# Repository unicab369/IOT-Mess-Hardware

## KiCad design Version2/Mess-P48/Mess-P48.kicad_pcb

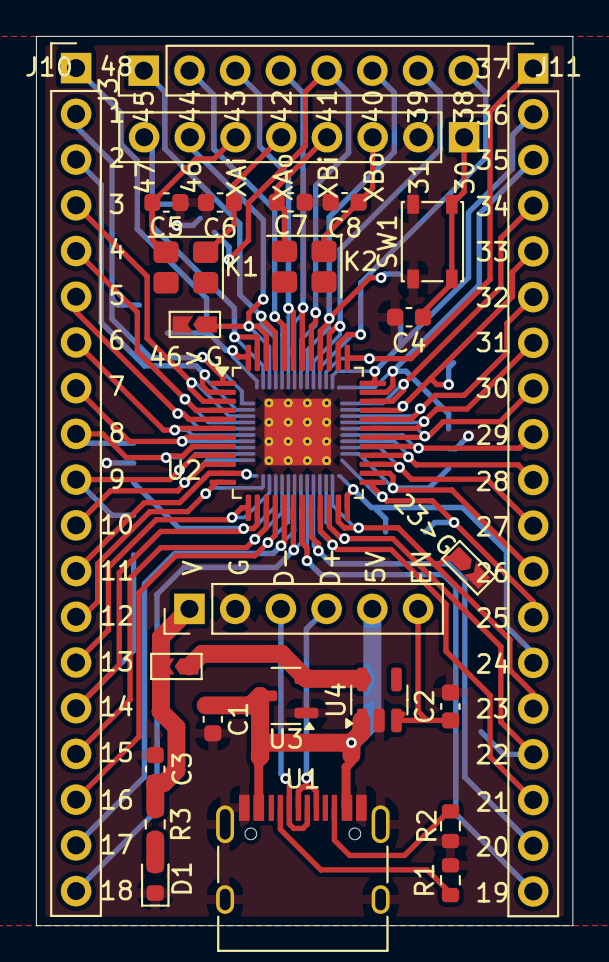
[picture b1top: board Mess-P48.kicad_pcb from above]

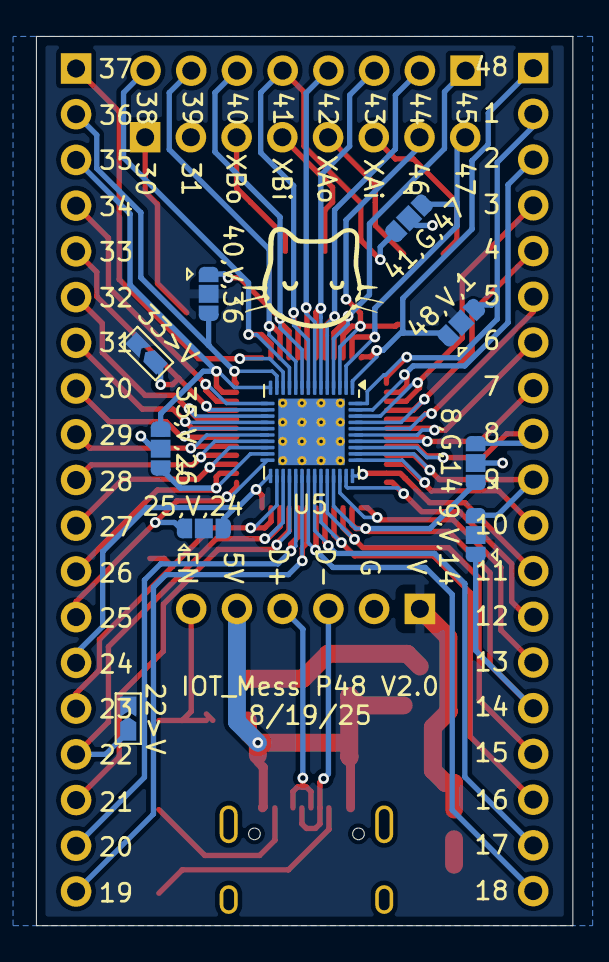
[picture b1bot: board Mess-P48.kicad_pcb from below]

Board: 2 copper layers, 29.8 x 49.4 mm, 37 parts (10 on the bottom side), 63 nets.

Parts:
8,G,14, 9,V,14, 25,V,24, 35,V,26, 40,V,36, 41,G,47, 48,V,1: Jumper; Jumper-3_P1.3mm_Open_RoundedPad1.0x1.5mm
22>V, 23>G, 33>V, 46>G: Jumper_2; Jumpper-triangle
C1: 10u; C_0603_1608Metric
C2, C3: 1u; C_0603_1608Metric
C4: .1u; C_0603_1608Metric
C5, C6: 15-30pF; C_0603_1608Metric
C7, C8: 12-25pF; C_0603_1608Metric
D1: LED; LED_0603_1608Metric
J1: Jumper_2; Jumpper-triangle
J2: Conn_01x06_Pin; PinHeader_1x06_P2.54mm_Vertical
J3, J4: Conn_01x08_Pin; PinHeader_1x08_P2.54mm_Vertical
J10, J11: Conn_01x19_Pin; PinHeader_1x19_P2.54mm_Vertical
K1, K2: Crystal; Crystal_SMD_3225-4Pin_3.2x2.5mm
R1, R2: 5.1K; R_0603_1608Metric
R3: R; R_0603_1608Metric
SW1: SW_Push; SW_SPST_PTS810
U1: USB_C_Receptacle_USB2.0_16P; USB_C_Receptacle_HRO_TYPE-C-31-M-12
U2: LQFP-48-1EP_7x7mm_P0.5mm_EP3.6x3.6mm
U3: XC6206PxxxMR; SOT-23-3
U4: ME6211C33M5; SOT-23-5
U5: CH32L103C8T6; QFN-48-1EP_5x5mm_P0.35mm_EP3.7x3.7mm_ThermalVias

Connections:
5V: C1.1, J2.5, U1.A4 (VBUS), U1.A9 (VBUS), U1.B4 (VBUS), U1.B9 (VBUS), U3.3 (VI), U4.1 (V_{IN})
D+: J2.4, U1.A6 (D+), U1.B6 (D+)
D-: J2.3, U1.A7 (D-), U1.B7 (D-)
EN: C2.1, J2.6, U4.3 (CE)
GND: 8,G,14.2 (C), 23>G.2 (B), 35,V,26.2 (C), 41,G,47.2 (C), 46>G.2 (B), C1.2, C2.2, C3.2, C4.2, C5.2, C6.2, C7.2, C8.2, D1.1 (K), J2.2, J4.2, R1.2, R2.2, SW1.2, U1.A1 (GND), U1.A12 (GND), U1.B1 (GND), U1.B12 (GND), U1.S1 (SHIELD), U2.49 (VSS), U3.1 (GND), U4.2 (V_{SS}), U5.49 (VSS)
unnamed: D1.2 (A), R3.2
unnamed: J1.1 (A), U3.2 (VO), U4.5 (V_{OUT})
unnamed: C4.1, J4.1, SW1.1
unnamed: C8.1, J4.3, K2.1
unnamed: C7.1, J4.4, K2.2
unnamed: C6.1, J4.5, K1.1
unnamed: C5.1, J4.6, K1.2
unnamed: R1.1, U1.A5 (CC1)
unnamed: R2.1, U1.B5 (CC2)
P_1: 48,V,1.3 (B), J10.2, U2.1 (VBAT), U5.48 (VDD_3)
P_2: J10.3, U2.2 (PC13), U5.47 (VSS_3)
P_3: J10.4, U2.3 (PC14/OSC32_IN), U5.46 (PB9)
P_4: J10.5, U2.4 (PC15/OSC32_OUT), U5.45 (PB8)
P_5: J10.6, U2.5 (PD0/OSC_IN), U5.44 (BOOT0)
P_6: J10.7, U2.6 (PD1/OSC_OUT), U5.43 (PB7/USB2_DP/SDA*)
P_7: J10.8, U2.7 (NRST), U5.42 (PB6/USB2_DM/SCL*)
P_8: 8,G,14.3 (B), J10.9, U2.8 (VSSA), U5.41 (PB5)
P_9: 9,V,14.3 (B), J10.10, U2.9 (VDDA), U5.40 (PB4)
P_10: J10.11, U2.10 (PA0/ADC0/WKUP), U5.39 (PB3)
P_11: J10.12, U2.11 (PA1/ADC1), U5.38 (PA15)
P_12: J10.13, U2.12 (PA2/ADC2), U5.37 (PA14/SWCLK)
P_13: J10.14, U2.13 (PA3/ADC3), U5.36 (VDD_2)
P_14: 8,G,14.1 (A), 9,V,14.1 (A), J10.15, U2.14 (PA4/ADC), U5.35 (VSS_2)
P_15: J10.16, U2.15 (PA5/ADC5/SCK*), U5.34 (PA23/SWDIO)
P_16: J10.17, U2.16 (PA6/ADC6/MISO*), U5.33 (PA12/USB_HDP)
P_17: J10.18, U2.17 (PA7/ADC7/MOSI*), U5.32 (PA11/USB_HDM)
P_18: J10.19, U2.18 (PB0/ADC8), U5.31 (PA10)
P_19: J11.19, U2.19 (PB1/ADC9), U5.30 (PA9)
P_20: J11.18, U2.20 (PB2/BOTT), U5.29 (PA8)
P_21: J11.17, U2.21 (PB10/SCL2*), U5.28 (PD15/MOSI_2*)
P_22: 22>V.1 (A), J11.16, U2.22 (PB11/SDA2*), U5.27 (PD14/MISO_2*)
P_23: 23>G.1 (A), J11.15, U2.23 (VSS_1), U5.26 (PD13/SCK_2*)
P_24: 25,V,24.3 (B), J11.14, U2.24 (VDD_VIO_1), U5.25 (PD12)
P_25: 25,V,24.1 (A), J11.13, U2.25 (PB12), U5.24 (VDD_1)
P_26: 35,V,26.1 (A), J11.12, U2.26 (PB13/SCK2*), U5.23 (VSS_1)
P_27: J11.11, U2.27 (PB14/MISO2*), U5.22 (BP11/SDA2*)
P_28: J11.10, U2.28 (PB15/MOSI2*), U5.21 (PB10/SCL2*)
P_29: J11.9, U2.29 (PA8), U5.20 (PB2/BOOT)
P_30: J11.8, U2.30 (PA9), U5.19 (PB1/ADC9)
P_31: J11.7, U2.31 (PA10), U5.18 (PB0/ADC8)
P_32: J11.6, U2.32 (PA11/USB1_DM), U5.17 (PA7/ADC7/MOSI*)
P_33: 33>V.1 (A), J11.5, U2.33 (PA12/USB1_DP), U5.16 (PA6/ADC6/MISO*)
P_34: J11.4, U2.34 (AP13/SWDIO), U5.15 (PA5/ADC5/ADC1/SCK*)
P_35: 35,V,26.3 (B), J11.3, U2.35 (VSS_2), U5.14 (PA4/ADC4/ADC0)
P_36: 40,V,36.3 (B), J11.2, U2.36 (VDD_2), U5.13 (PA3/ADC3)
P_37: J11.1, U2.37 (PA14/SWCLK), U5.12 (PA2/ADC2)
P_38: J3.8, U2.38 (PA15), U5.11 (PA1/ADC1)
P_39: J3.7, U2.39 (PB3), U5.10 (PA0/ADC0/WKUP)
P_40: 40,V,36.1 (A), J3.6, U2.40 (PB4), U5.9 (VDDA)
P_41: 41,G,47.3 (B), J3.5, U2.41 (PB5), U5.8 (VSSA)
P_42: J3.4, U2.42 (PB6/USB2_DM/SCL*), U5.7 (NRST)
P_43: J3.3, U2.43 (PB7/USB2_DP/SDA*), U5.6 (PD1/OSC_OUT)
P_44: J3.2, U2.44 (BOOT0), U5.5 (PD0/OSC_IN)
P_45: J3.1, U2.45 (PB8), U5.4 (PC15/OSC32_OUT)
P_46: 46>G.1 (A), J4.7, U2.46 (PB9), U5.3 (PC14/OSC32_IN)
P_47: 41,G,47.1 (A), J4.8, U2.47 (VSS_3), U5.2 (PC13)
P_48: 48,V,1.1 (A), J10.1, U2.48 (VDD_VIO_3), U5.1 (VBAT)
VCC: 9,V,14.2 (C), 22>V.2 (B), 25,V,24.2 (C), 33>V.2 (B), 40,V,36.2 (C), 48,V,1.2 (C), C3.1, J1.2 (B), J2.1, R3.1

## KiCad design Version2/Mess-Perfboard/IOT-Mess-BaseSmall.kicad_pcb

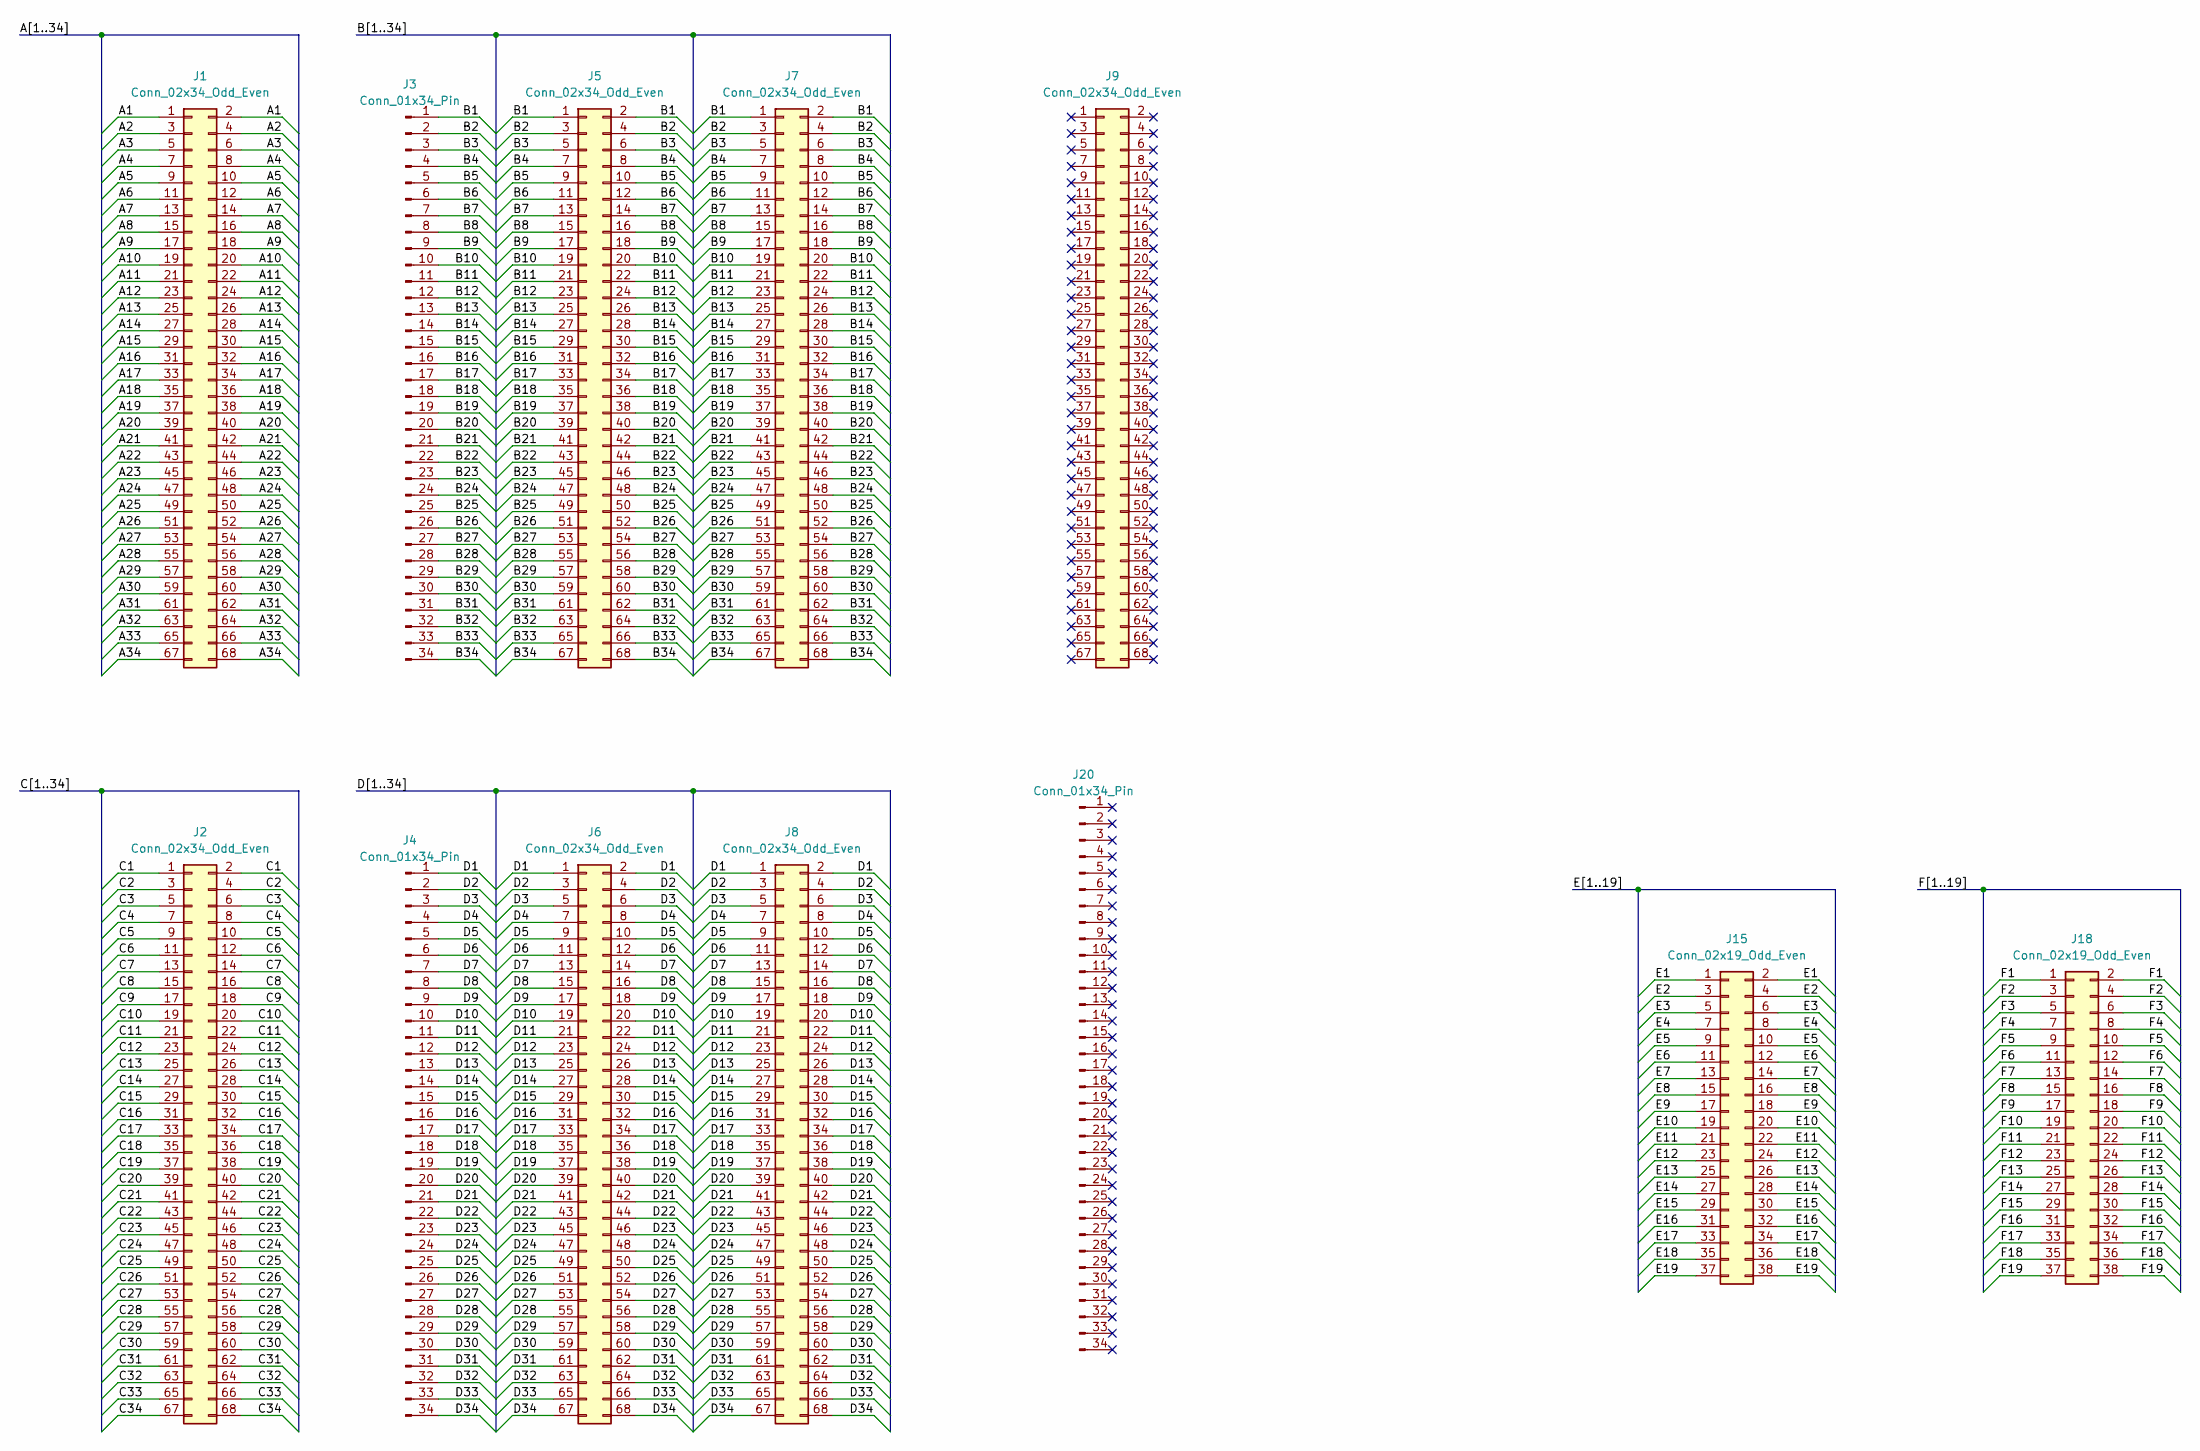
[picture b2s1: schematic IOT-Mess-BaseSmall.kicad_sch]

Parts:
J1, J2, J5, J6, J7, J8, J9: Conn_02x34_Odd_Even; PinSocket_2x34_P2.54mm_Vertical
J3, J4, J20: Conn_01x34_Pin; PinHeader_1x34_P2.54mm_Vertical
J15, J18: Conn_02x19_Odd_Even; PinHeader_2x19_P2.54mm_Vertical

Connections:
/A1: J1.1, J1.2
/A2: J1.3, J1.4
/A3: J1.5, J1.6
/A4: J1.7, J1.8
/A5: J1.9, J1.10
/A6: J1.11, J1.12
/A7: J1.13, J1.14
/A8: J1.15, J1.16
/A9: J1.17, J1.18
/A10: J1.19, J1.20
/A11: J1.21, J1.22
/A12: J1.23, J1.24
/A13: J1.25, J1.26
/A14: J1.27, J1.28
/A15: J1.29, J1.30
/A16: J1.31, J1.32
/A17: J1.33, J1.34
/A18: J1.35, J1.36
/A19: J1.37, J1.38
/A20: J1.39, J1.40
/A21: J1.41, J1.42
/A22: J1.43, J1.44
/A23: J1.45, J1.46
/A24: J1.47, J1.48
/A25: J1.49, J1.50
/A26: J1.51, J1.52
/A27: J1.53, J1.54
/A28: J1.55, J1.56
/A29: J1.57, J1.58
/A30: J1.59, J1.60
/A31: J1.61, J1.62
/A32: J1.63, J1.64
/A33: J1.65, J1.66
/A34: J1.67, J1.68
/B1: J3.1, J5.1, J5.2, J7.1, J7.2
/B2: J3.2, J5.3, J5.4, J7.3, J7.4
/B3: J3.3, J5.5, J5.6, J7.5, J7.6
/B4: J3.4, J5.7, J5.8, J7.7, J7.8
/B5: J3.5, J5.9, J5.10, J7.9, J7.10
/B6: J3.6, J5.11, J5.12, J7.11, J7.12
/B7: J3.7, J5.13, J5.14, J7.13, J7.14
/B8: J3.8, J5.15, J5.16, J7.15, J7.16
/B9: J3.9, J5.17, J5.18, J7.17, J7.18
/B10: J3.10, J5.19, J5.20, J7.19, J7.20
/B11: J3.11, J5.21, J5.22, J7.21, J7.22
/B12: J3.12, J5.23, J5.24, J7.23, J7.24
/B13: J3.13, J5.25, J5.26, J7.25, J7.26
/B14: J3.14, J5.27, J5.28, J7.27, J7.28
/B15: J3.15, J5.29, J5.30, J7.29, J7.30
/B16: J3.16, J5.31, J5.32, J7.31, J7.32
/B17: J3.17, J5.33, J5.34, J7.33, J7.34
/B18: J3.18, J5.35, J5.36, J7.35, J7.36
/B19: J3.19, J5.37, J5.38, J7.37, J7.38
/B20: J3.20, J5.39, J5.40, J7.39, J7.40
/B21: J3.21, J5.41, J5.42, J7.41, J7.42
/B22: J3.22, J5.43, J5.44, J7.43, J7.44
/B23: J3.23, J5.45, J5.46, J7.45, J7.46
/B24: J3.24, J5.47, J5.48, J7.47, J7.48
/B25: J3.25, J5.49, J5.50, J7.49, J7.50
/B26: J3.26, J5.51, J5.52, J7.51, J7.52
/B27: J3.27, J5.53, J5.54, J7.53, J7.54
/B28: J3.28, J5.55, J5.56, J7.55, J7.56
/B29: J3.29, J5.57, J5.58, J7.57, J7.58
/B30: J3.30, J5.59, J5.60, J7.59, J7.60
/B31: J3.31, J5.61, J5.62, J7.61, J7.62
/B32: J3.32, J5.63, J5.64, J7.63, J7.64
/B33: J3.33, J5.65, J5.66, J7.65, J7.66
/B34: J3.34, J5.67, J5.68, J7.67, J7.68
/C1: J2.1, J2.2
/C2: J2.3, J2.4
/C3: J2.5, J2.6
/C4: J2.7, J2.8
/C5: J2.9, J2.10
/C6: J2.11, J2.12
/C7: J2.13, J2.14
/C8: J2.15, J2.16
/C9: J2.17, J2.18
/C10: J2.19, J2.20
/C11: J2.21, J2.22
/C12: J2.23, J2.24
/C13: J2.25, J2.26
/C14: J2.27, J2.28
/C15: J2.29, J2.30
/C16: J2.31, J2.32
/C17: J2.33, J2.34
/C18: J2.35, J2.36
/C19: J2.37, J2.38
/C20: J2.39, J2.40
/C21: J2.41, J2.42
/C22: J2.43, J2.44
/C23: J2.45, J2.46
/C24: J2.47, J2.48
/C25: J2.49, J2.50
/C26: J2.51, J2.52
/C27: J2.53, J2.54
/C28: J2.55, J2.56
/C29: J2.57, J2.58
/C30: J2.59, J2.60
/C31: J2.61, J2.62
/C32: J2.63, J2.64
/C33: J2.65, J2.66
/C34: J2.67, J2.68
/D1: J4.1, J6.1, J6.2, J8.1, J8.2
/D2: J4.2, J6.3, J6.4, J8.3, J8.4
/D3: J4.3, J6.5, J6.6, J8.5, J8.6
/D4: J4.4, J6.7, J6.8, J8.7, J8.8
/D5: J4.5, J6.9, J6.10, J8.9, J8.10
/D6: J4.6, J6.11, J6.12, J8.11, J8.12
/D7: J4.7, J6.13, J6.14, J8.13, J8.14
/D8: J4.8, J6.15, J6.16, J8.15, J8.16
/D9: J4.9, J6.17, J6.18, J8.17, J8.18
/D10: J4.10, J6.19, J6.20, J8.19, J8.20
/D11: J4.11, J6.21, J6.22, J8.21, J8.22
/D12: J4.12, J6.23, J6.24, J8.23, J8.24
/D13: J4.13, J6.25, J6.26, J8.25, J8.26
/D14: J4.14, J6.27, J6.28, J8.27, J8.28
/D15: J4.15, J6.29, J6.30, J8.29, J8.30
/D16: J4.16, J6.31, J6.32, J8.31, J8.32
/D17: J4.17, J6.33, J6.34, J8.33, J8.34
/D18: J4.18, J6.35, J6.36, J8.35, J8.36
/D19: J4.19, J6.37, J6.38, J8.37, J8.38
/D20: J4.20, J6.39, J6.40, J8.39, J8.40
/D21: J4.21, J6.41, J6.42, J8.41, J8.42
/D22: J4.22, J6.43, J6.44, J8.43, J8.44
/D23: J4.23, J6.45, J6.46, J8.45, J8.46
/D24: J4.24, J6.47, J6.48, J8.47, J8.48
/D25: J4.25, J6.49, J6.50, J8.49, J8.50
/D26: J4.26, J6.51, J6.52, J8.51, J8.52
/D27: J4.27, J6.53, J6.54, J8.53, J8.54
/D28: J4.28, J6.55, J6.56, J8.55, J8.56
/D29: J4.29, J6.57, J6.58, J8.57, J8.58
/D30: J4.30, J6.59, J6.60, J8.59, J8.60
/D31: J4.31, J6.61, J6.62, J8.61, J8.62
/D32: J4.32, J6.63, J6.64, J8.63, J8.64
/D33: J4.33, J6.65, J6.66, J8.65, J8.66
/D34: J4.34, J6.67, J6.68, J8.67, J8.68
/E1: J15.1, J15.2
/E2: J15.3, J15.4
/E3: J15.5, J15.6
/E4: J15.7, J15.8
/E5: J15.9, J15.10
/E6: J15.11, J15.12
/E7: J15.13, J15.14
/E8: J15.15, J15.16
/E9: J15.17, J15.18
/E10: J15.19, J15.20
/E11: J15.21, J15.22
/E12: J15.23, J15.24
/E13: J15.25, J15.26
/E14: J15.27, J15.28
/E15: J15.29, J15.30
/E16: J15.31, J15.32
/E17: J15.33, J15.34
/E18: J15.35, J15.36
/E19: J15.37, J15.38
/F1: J18.1, J18.2
/F2: J18.3, J18.4
/F3: J18.5, J18.6
/F4: J18.7, J18.8
/F5: J18.9, J18.10
/F6: J18.11, J18.12
/F7: J18.13, J18.14
/F8: J18.15, J18.16
/F9: J18.17, J18.18
/F10: J18.19, J18.20
/F11: J18.21, J18.22
/F12: J18.23, J18.24
/F13: J18.25, J18.26
/F14: J18.27, J18.28
/F15: J18.29, J18.30
/F16: J18.31, J18.32
/F17: J18.33, J18.34
/F18: J18.35, J18.36
/F19: J18.37, J18.38

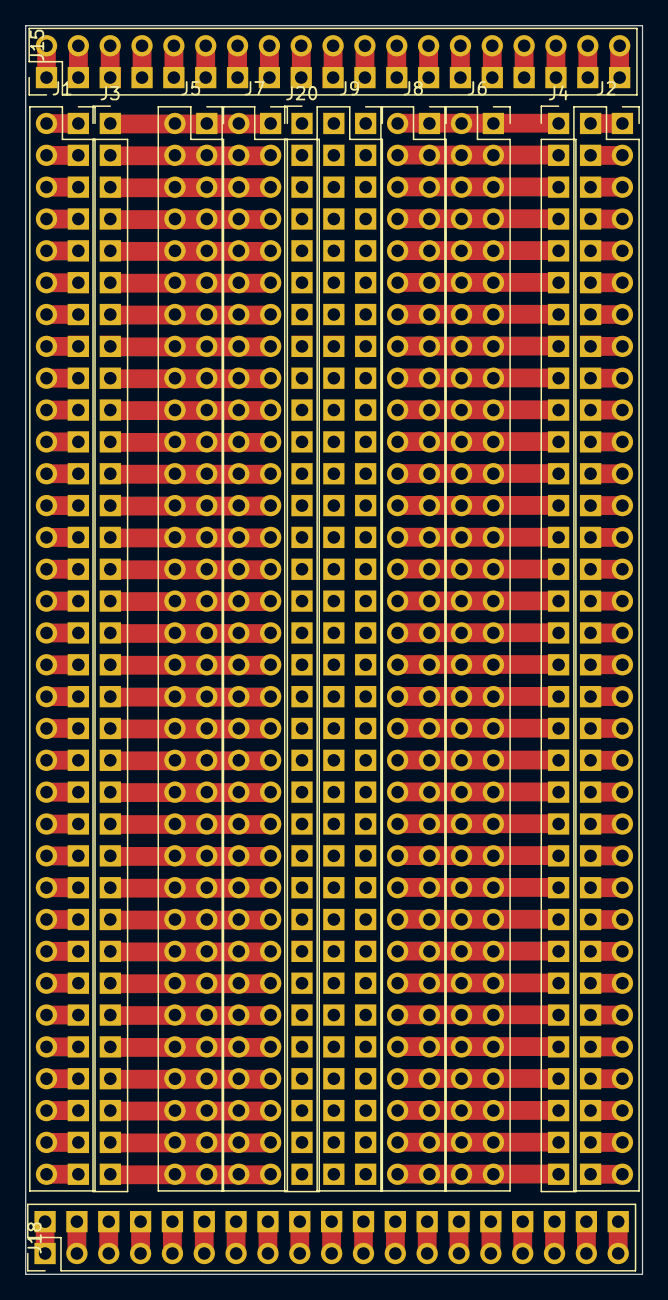
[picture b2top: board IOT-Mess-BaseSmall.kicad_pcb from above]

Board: 2 copper layers, 49.2 x 99.6 mm, 12 parts (0 on the bottom side), 174 nets.

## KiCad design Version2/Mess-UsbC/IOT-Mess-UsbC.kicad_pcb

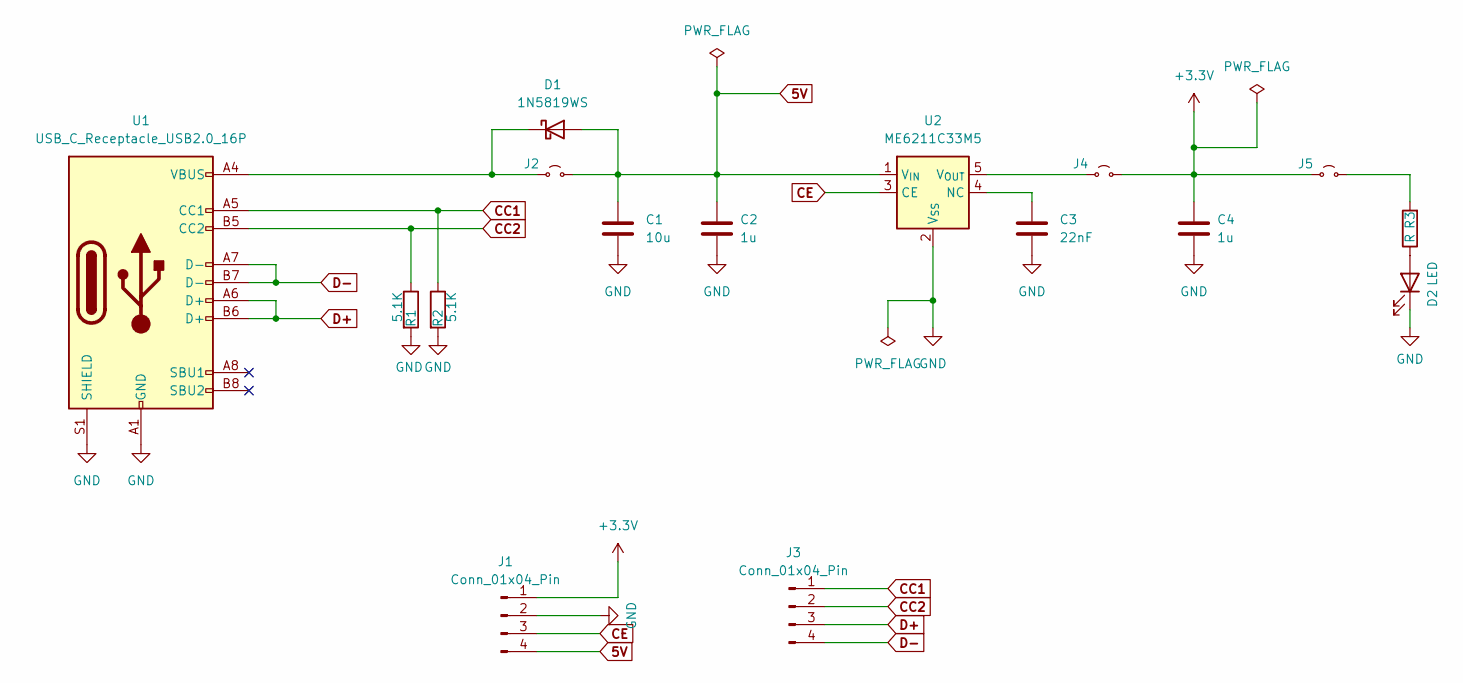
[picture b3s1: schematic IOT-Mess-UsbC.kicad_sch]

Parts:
C1: 10u; C_0603_1608Metric
C2, C4: 1u; C_0603_1608Metric
C3: 22nF; C_0603_1608Metric
D1: 1N5819WS; D_SOD-323
D2: LED; LED_0603_1608Metric
J1, J3: Conn_01x04_Pin; PinHeader_1x04_P2.54mm_Vertical
J2, J4, J5: Jumper_2; Jumpper-triangle
R1, R2: 5.1K; R_0603_1608Metric
R3: R; R_0603_1608Metric
U1: USB_C_Receptacle_USB2.0_16P; USB_C_Receptacle_HRO_TYPE-C-31-M-12
U2: ME6211C33M5; SOT-23-5

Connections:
5V: C1.1, C2.1, D1.2 (A), J1.4, J2.2 (B), U2.1 (V_{IN})
+3.3V: C4.1, J1.1, J4.2 (B), J5.1 (A)
CC1: J3.1, R2.1, U1.A5 (CC1)
CC2: J3.2, R1.1, U1.B5 (CC2)
CE: J1.3, U2.3 (CE)
D+: J3.3, U1.A6 (D+), U1.B6 (D+)
D-: J3.4, U1.A7 (D-), U1.B7 (D-)
GND: C1.2, C2.2, C3.2, C4.2, D2.1 (K), J1.2, R1.2, R2.2, U1.A1 (GND), U1.A12 (GND), U1.B1 (GND), U1.B12 (GND), U1.S1 (SHIELD), U2.2 (V_{SS})
unnamed: D1.1 (K), J2.1 (A), U1.A4 (VBUS), U1.A9 (VBUS), U1.B4 (VBUS), U1.B9 (VBUS)
unnamed: D2.2 (A), R3.1
unnamed: J4.1 (A), U2.5 (V_{OUT})
unnamed: J5.2 (B), R3.2
unnamed: C3.1, U2.4 (NC)

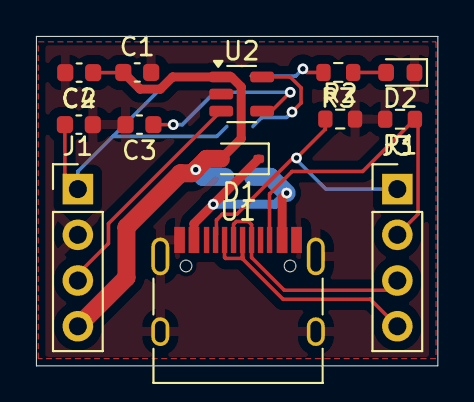
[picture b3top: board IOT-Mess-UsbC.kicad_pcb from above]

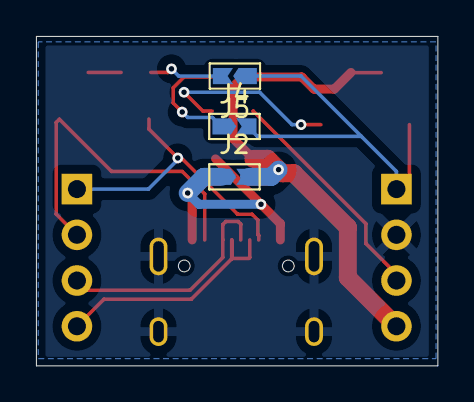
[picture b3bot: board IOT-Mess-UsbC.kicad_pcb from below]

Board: 2 copper layers, 22.3 x 18.3 mm, 16 parts (3 on the bottom side), 13 nets.

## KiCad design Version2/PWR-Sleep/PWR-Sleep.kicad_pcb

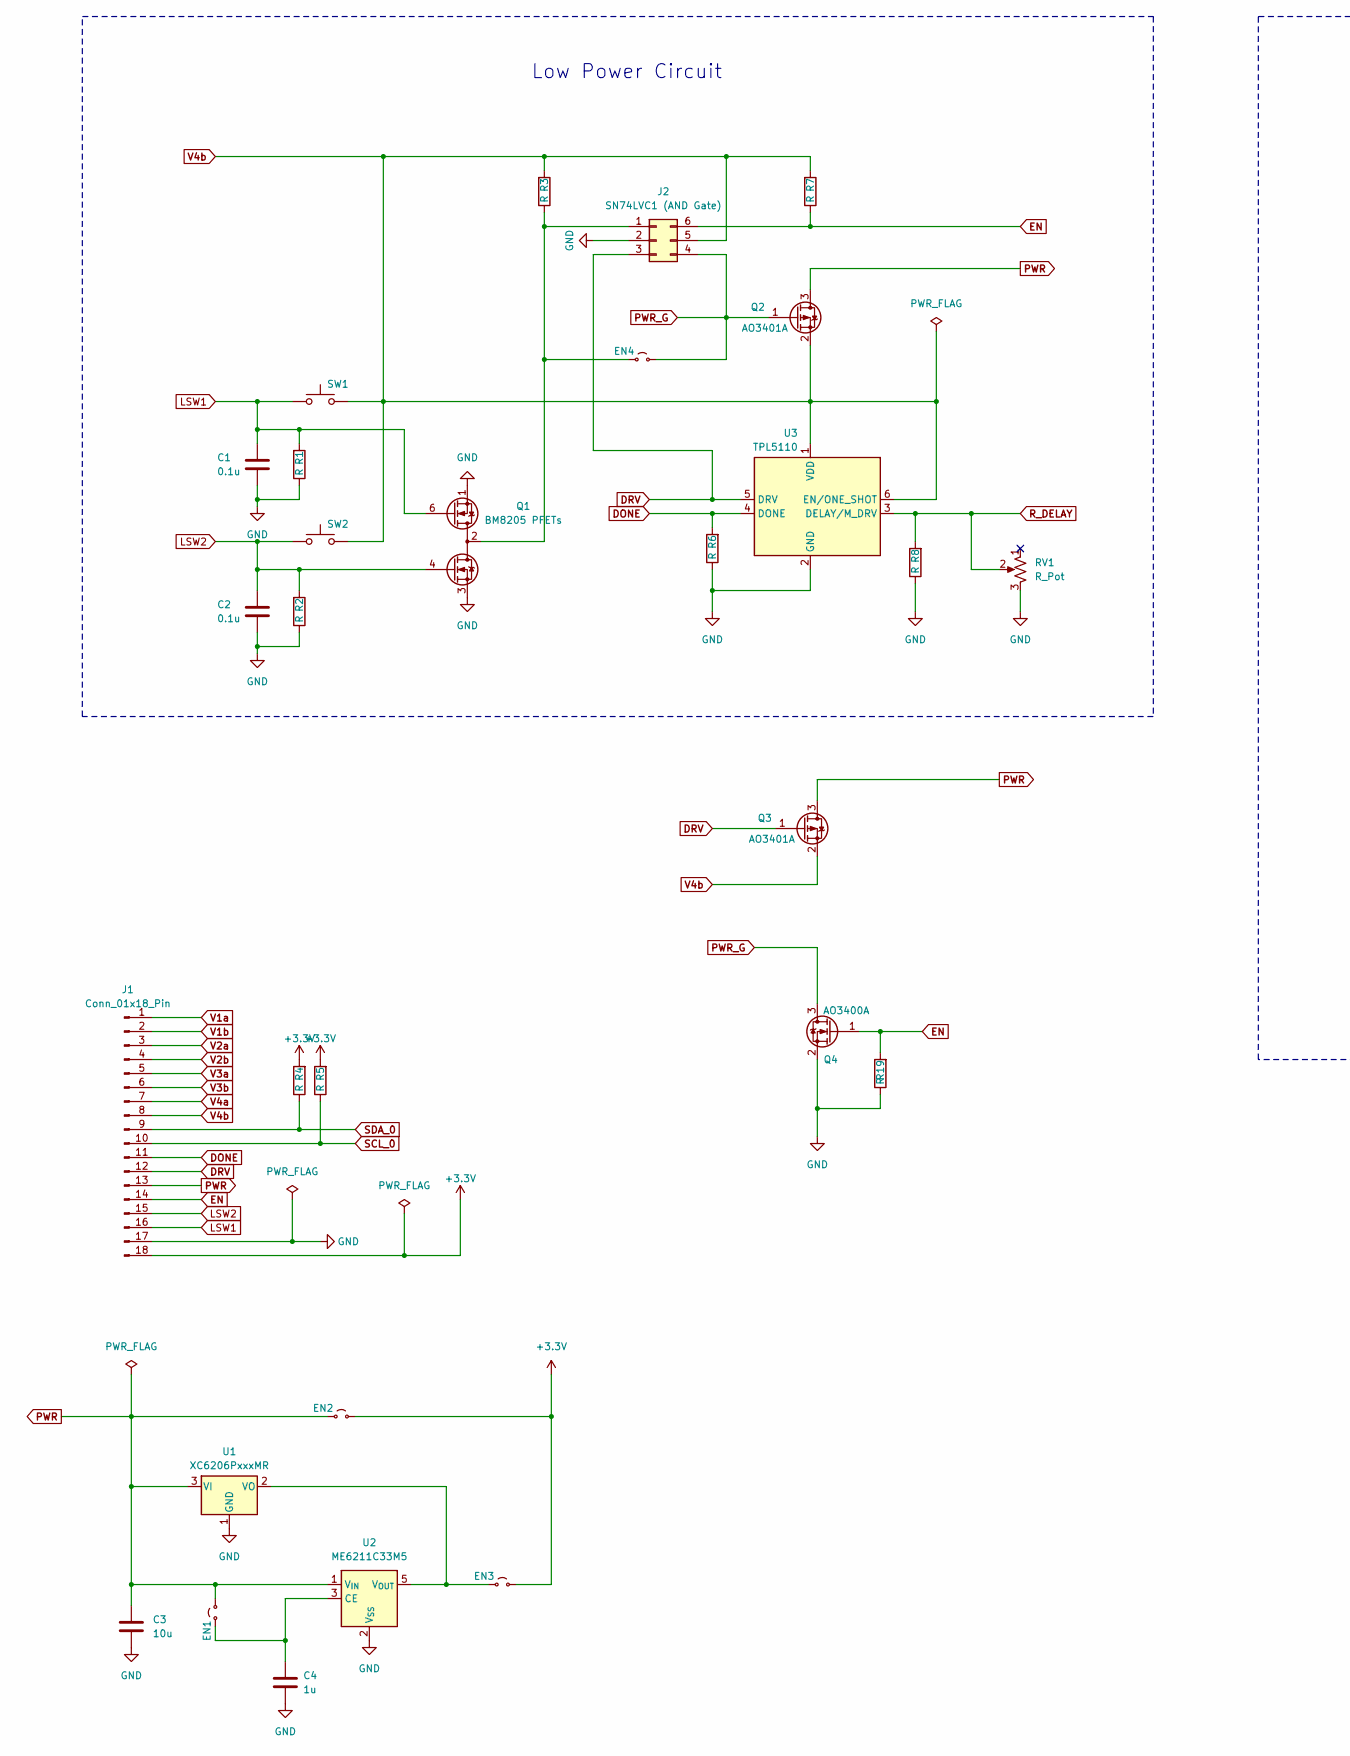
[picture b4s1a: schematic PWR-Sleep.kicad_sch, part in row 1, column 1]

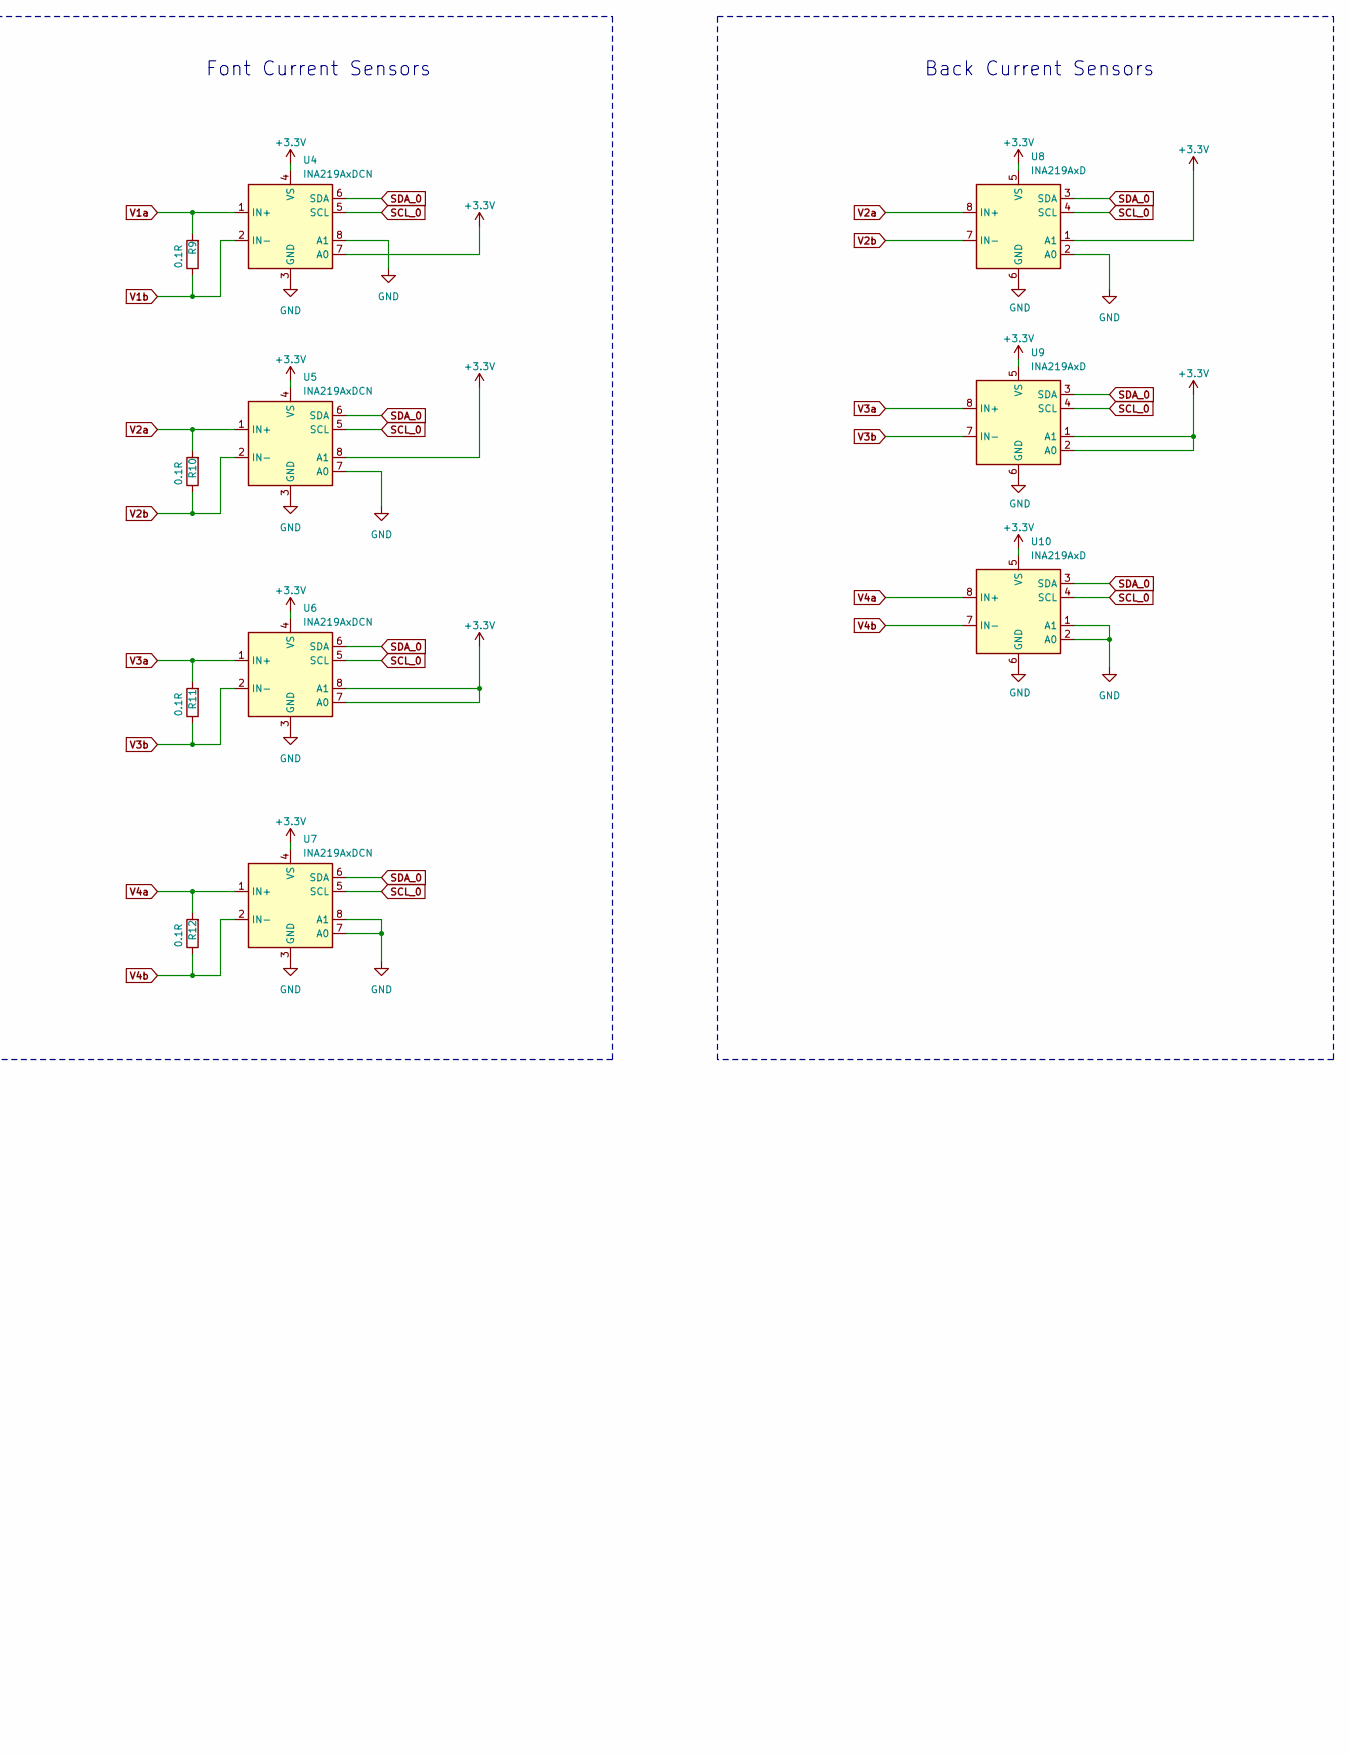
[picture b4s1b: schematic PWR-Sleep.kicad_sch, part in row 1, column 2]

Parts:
C1, C2: 0.1u; C_0603_1608Metric
C3: 10u; C_0603_1608Metric
C4: 1u; C_0603_1608Metric
EN1, EN2, EN3, EN4: Jumper_2; Jumpper-triangle
J1: Conn_01x18_Pin; PinHeader_1x18_P2.54mm_Vertical
J2: SN74LVC1 (AND Gate); SOT-23-6
Q1: BM8205 PFETs; SOT-23-6
Q2, Q3: AO3401A; SOT-23
Q4: AO3400A; SOT-23
R1, R2, R3, R4, R5, R6, R7, R8, R19: R; R_0603_1608Metric
R9, R10, R11, R12: 0.1R; R_2512_6332Metric
RV1: R_Pot; Potentiometer_Piher_PT-6-V_Vertical
SW1, SW2: SW_Push; SW_SPST_PTS810
U1: XC6206PxxxMR; SOT-23-3
U2: ME6211C33M5; SOT-23-5
U3: TPL5110; SOT-23-6
U4, U5, U6, U7: INA219AxDCN; SOT-23-8
U8, U9, U10: INA219AxD; SOIC-8_3.9x4.9mm_P1.27mm

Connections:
+3.3V: EN2.2 (B), EN3.2 (B), J1.18, R4.2, R5.2, U4.4 (VS), U4.7 (A0), U5.4 (VS), U5.8 (A1), U6.4 (VS), U6.7 (A0), U6.8 (A1), U7.4 (VS), U8.1 (A1), U8.5 (VS), U9.1 (A1), U9.2 (A0), U9.5 (VS), U10.5 (VS)
DONE: J1.11, R6.2, U3.4 (DONE)
DRV: J1.12, J2.3, Q3.1 (G), U3.5 (DRV)
EN: J1.14, J2.6, Q4.1 (G), R7.1, R19.2
GND: C1.2, C2.2, C3.2, C4.2, J1.17, J2.2, Q1.1 (D1), Q1.3 (S2), Q4.2 (S), R1.1, R2.1, R6.1, R8.1, R19.1, RV1.3, U1.1 (GND), U2.2 (V_{SS}), U3.2 (GND), U4.3 (GND), U4.8 (A1), U5.3 (GND), U5.7 (A0), U6.3 (GND), U7.3 (GND), U7.7 (A0), U7.8 (A1), U8.2 (A0), U8.6 (GND), U9.6 (GND), U10.1 (A1), U10.2 (A0), U10.6 (GND)
LSW1: C1.1, J1.16, Q1.6 (G1), R1.2, SW1.2
LSW2: C2.1, J1.15, Q1.4 (G2), R2.2, SW2.2
unnamed: C4.1, EN1.1 (A), U2.3 (CE)
unnamed: EN3.1 (A), U1.2 (VO), U2.5 (V_{OUT})
unnamed: EN4.1 (A), J2.1, Q1.2 (S1/D2), Q1.5 (S1/D2), R3.1
PWR: C3.1, EN1.2 (B), EN2.1 (A), J1.13, Q2.3 (D), Q3.3 (D), U1.3 (VI), U2.1 (V_{IN})
PWR_G: EN4.2 (B), J2.4, Q2.1 (G), Q4.3 (D)
R_DELAY: R8.2, RV1.2, U3.3 (DELAY/M_DRV)
SCL_0: J1.10, R5.1, U4.5 (SCL), U5.5 (SCL), U6.5 (SCL), U7.5 (SCL), U8.4 (SCL), U9.4 (SCL), U10.4 (SCL)
SDA_0: J1.9, R4.1, U4.6 (SDA), U5.6 (SDA), U6.6 (SDA), U7.6 (SDA), U8.3 (SDA), U9.3 (SDA), U10.3 (SDA)
V1a: J1.1, R9.2, U4.1 (IN+)
V1b: J1.2, R9.1, U4.2 (IN-)
V2a: J1.3, R10.2, U5.1 (IN+), U8.8 (IN+)
V2b: J1.4, R10.1, U5.2 (IN-), U8.7 (IN-)
V3a: J1.5, R11.2, U6.1 (IN+), U9.8 (IN+)
V3b: J1.6, R11.1, U6.2 (IN-), U9.7 (IN-)
V4a: J1.7, R12.2, U7.1 (IN+), U10.8 (IN+)
V4b: J1.8, J2.5, Q2.2 (S), Q3.2 (S), R3.2, R7.2, R12.1, SW1.1, SW2.1, U3.1 (VDD), U3.6 (EN/ONE_SHOT), U7.2 (IN-), U10.7 (IN-)

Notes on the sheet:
Font Current Sensors
Low Power Circuit
Back Current Sensors

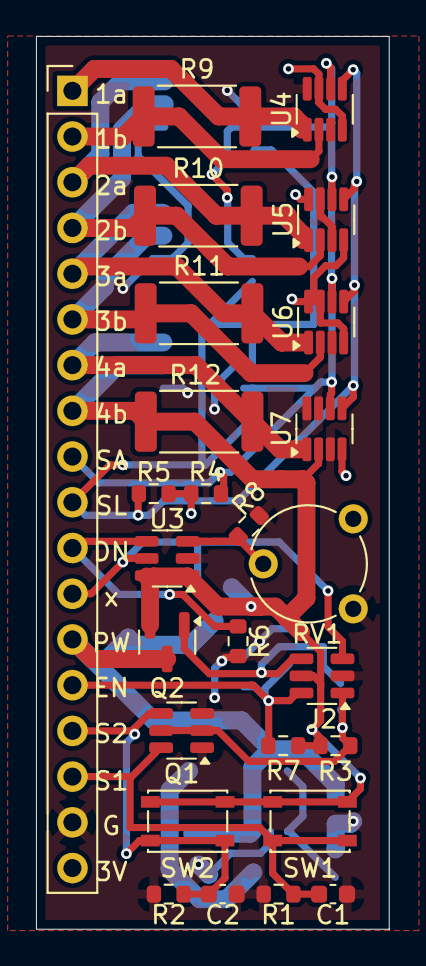
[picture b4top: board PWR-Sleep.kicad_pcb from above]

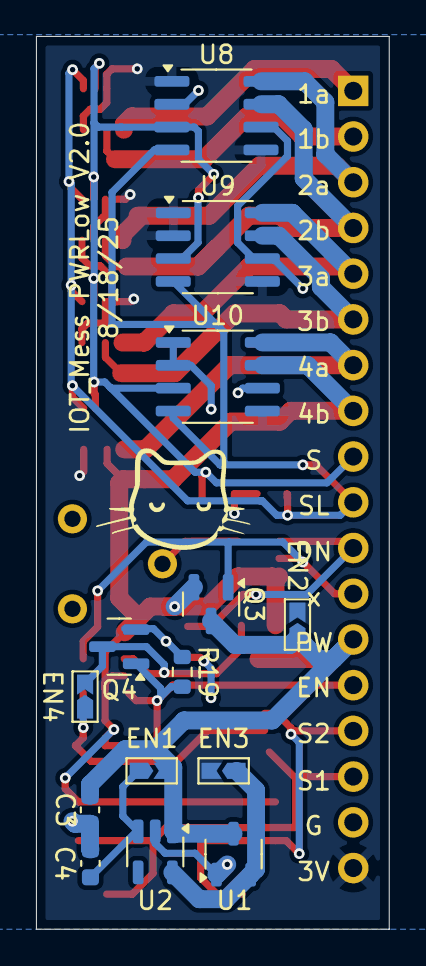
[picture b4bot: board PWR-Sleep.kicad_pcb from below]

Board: 2 copper layers, 19.6 x 49.6 mm, 40 parts (14 on the bottom side), 23 nets.
